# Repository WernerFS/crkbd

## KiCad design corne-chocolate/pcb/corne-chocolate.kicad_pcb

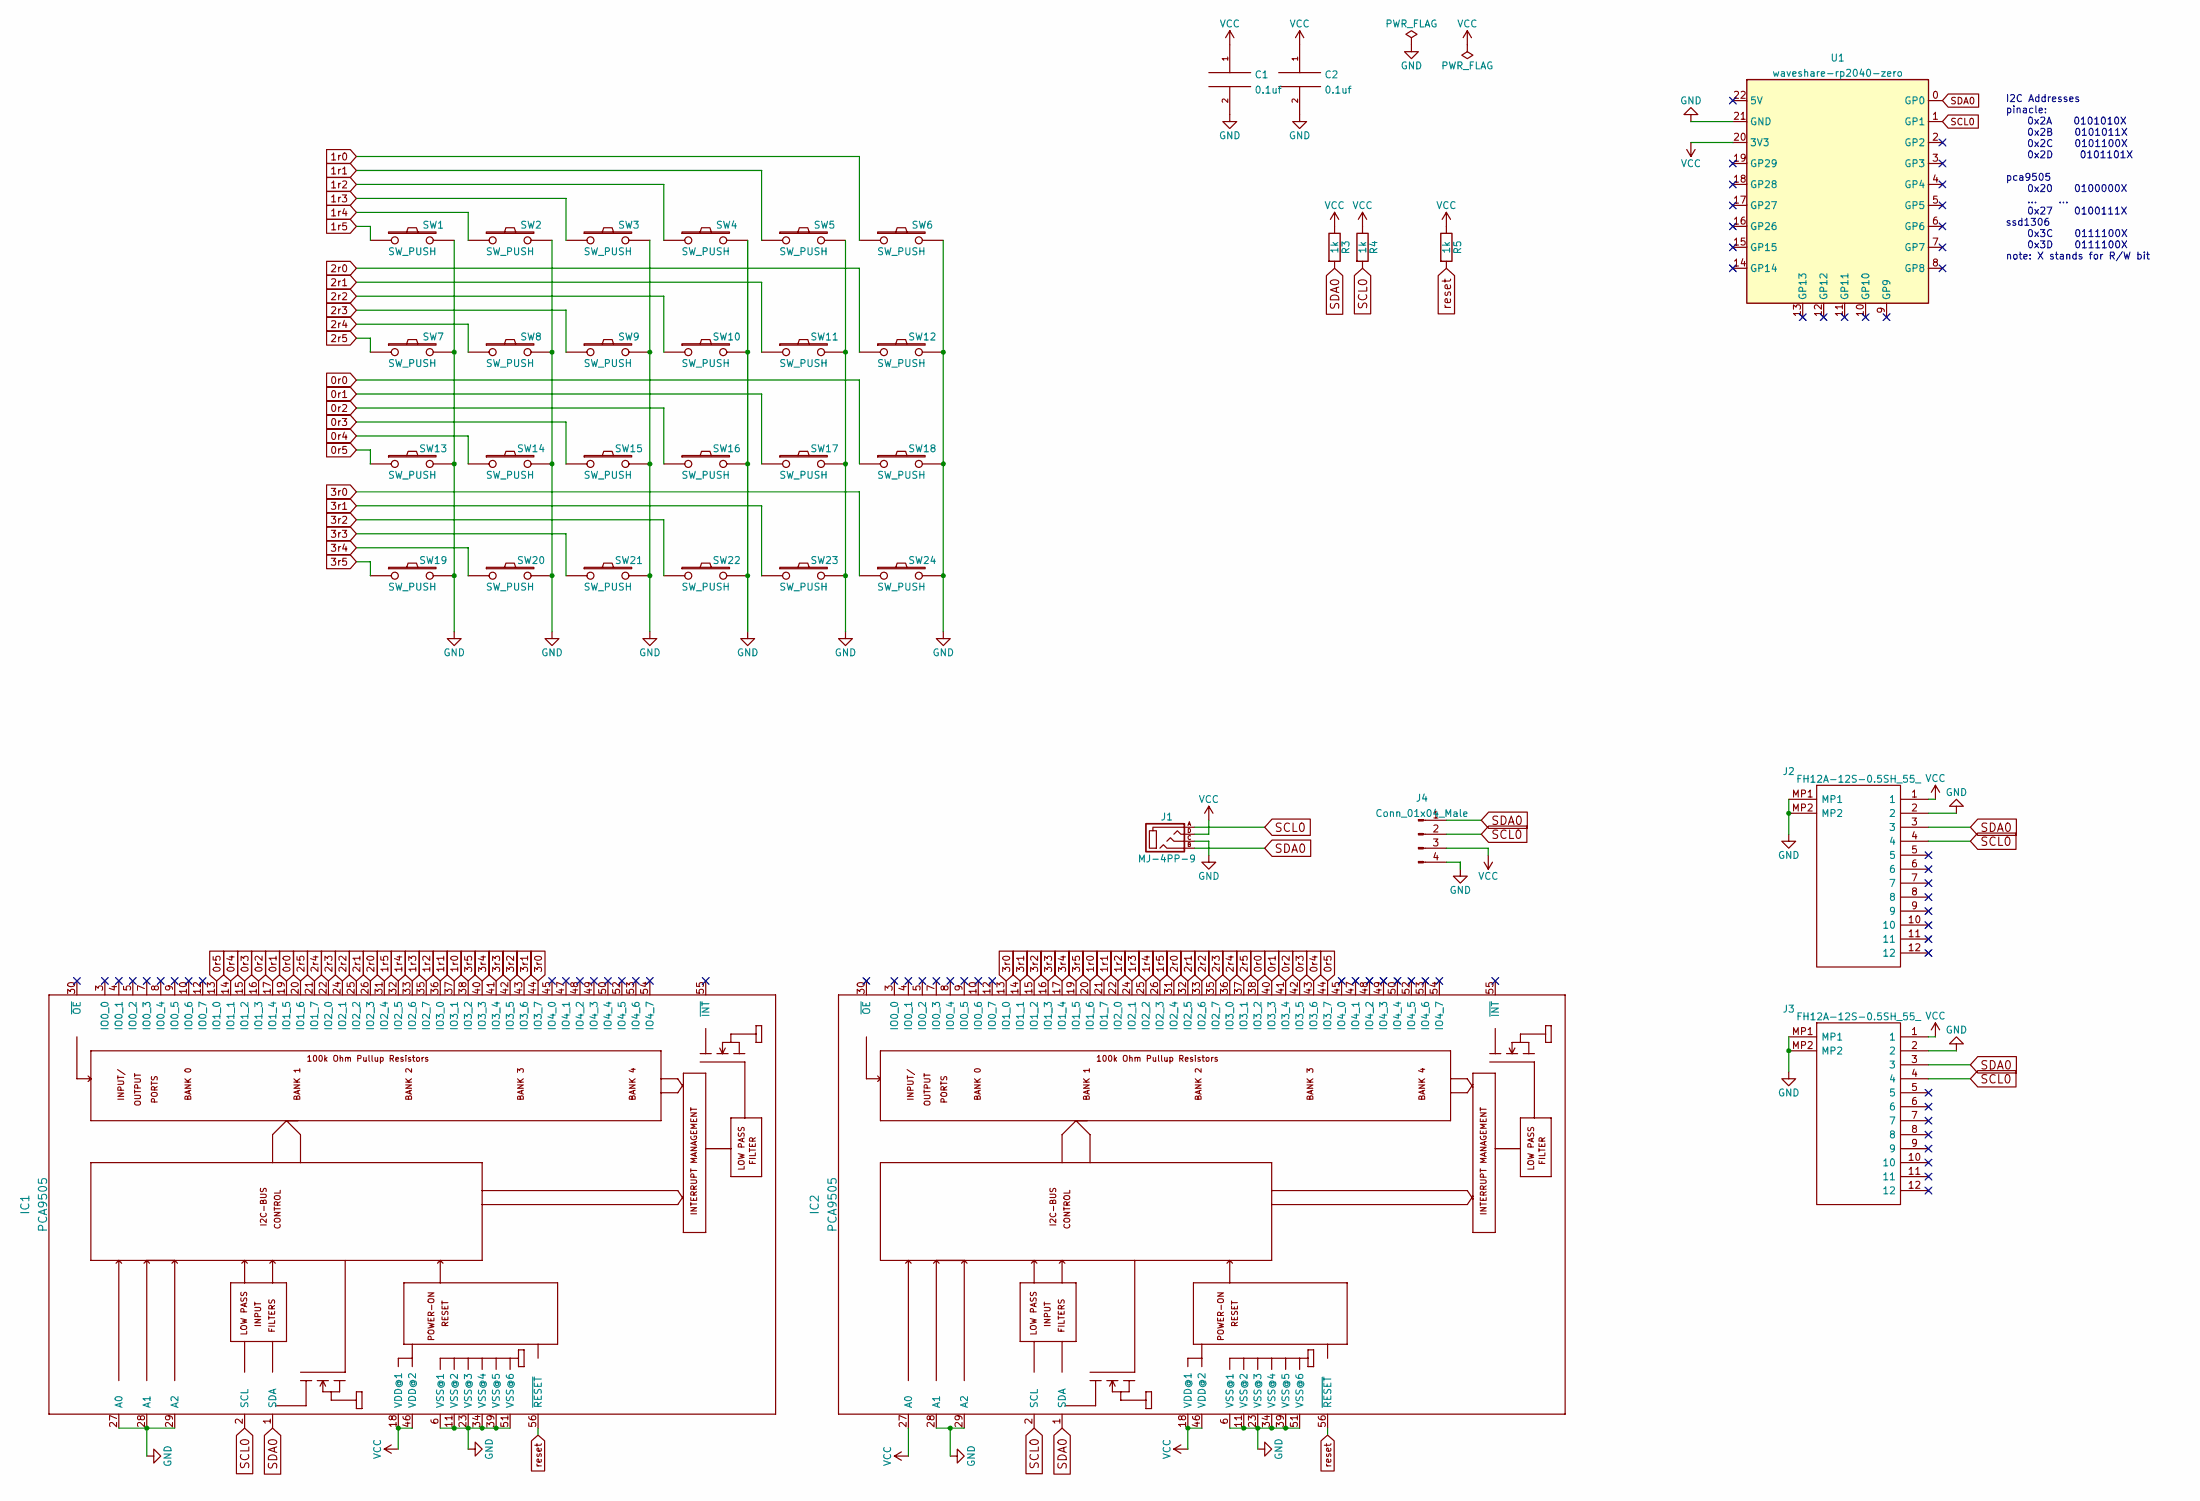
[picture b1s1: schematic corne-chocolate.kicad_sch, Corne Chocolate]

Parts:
C1, C2: 0.1uf; C_0805_2012Metric_Pad1.18x1.45mm_HandSolder
IC1, IC2: PCA9505; TSSOP-56_7x14mm_P0.5mm_mr
J1: MJ-4PP-9; 4-ring-jack-mr
J2, J3: FH12A-12S-0.5SH_55_; FH12A12S05SH55; Mouser Part Number 798-FH12A-12S0.5SH55
J4: Conn_01x04_Male; PinHeader_1x04_P2.54mm_Vertical
R3, R4, R5: 1k; R_0805_2012Metric_Pad1.20x1.40mm_HandSolder
SW1, SW2, SW3, SW4, SW5, SW6, SW7, SW8, SW9, SW10, SW11, SW12, SW13, SW14, SW15, SW16, SW17, SW18, SW19, SW20, SW21, SW22, SW23, SW24: SW_PUSH; kbd-switches
U1: waveshare-rp2040-zero; rp2040-zero-mr

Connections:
0r0: IC1.19 (IO1_5), IC2.38 (IO3_2), SW18.1
0r1: IC1.17 (IO1_4), IC2.40 (IO3_3), SW17.1
0r2: IC1.16 (IO1_3), IC2.41 (IO3_4), SW16.1
0r3: IC1.15 (IO1_2), IC2.42 (IO3_5), SW15.1
0r4: IC1.14 (IO1_1), IC2.43 (IO3_6), SW14.1
0r5: IC1.13 (IO1_0), IC2.44 (IO3_7), SW13.1
1r0: IC1.37 (IO3_1), IC2.20 (IO1_6), SW6.1
1r1: IC1.36 (IO3_0), IC2.21 (IO1_7), SW5.1
1r2: IC1.35 (IO2_7), IC2.22 (IO2_0), SW4.1
1r3: IC1.33 (IO2_6), IC2.24 (IO2_1), SW3.1
1r4: IC1.32 (IO2_5), IC2.25 (IO2_2), SW2.1
1r5: IC1.31 (IO2_4), IC2.26 (IO2_3), SW1.1
2r0: IC1.26 (IO2_3), IC2.31 (IO2_4), SW12.1
2r1: IC1.25 (IO2_2), IC2.32 (IO2_5), SW11.1
2r2: IC1.24 (IO2_1), IC2.33 (IO2_6), SW10.1
2r3: IC1.22 (IO2_0), IC2.35 (IO2_7), SW9.1
2r4: IC1.21 (IO1_7), IC2.36 (IO3_0), SW8.1
2r5: IC1.20 (IO1_6), IC2.37 (IO3_1), SW7.1
3r0: IC1.44 (IO3_7), IC2.13 (IO1_0), SW24.1
3r1: IC1.43 (IO3_6), IC2.14 (IO1_1), SW23.1
3r2: IC1.42 (IO3_5), IC2.15 (IO1_2), SW22.1
3r3: IC1.41 (IO3_4), IC2.16 (IO1_3), SW21.1
3r4: IC1.40 (IO3_3), IC2.17 (IO1_4), SW20.1
3r5: IC1.38 (IO3_2), IC2.19 (IO1_5), SW19.1
GND: C1.2, C2.2, IC1.6 (VSS@1), IC1.11 (VSS@2), IC1.23 (VSS@3), IC1.27 (A0), IC1.28 (A1), IC1.29 (A2), IC1.34 (VSS@4), IC1.39 (VSS@5), IC1.51 (VSS@6), IC2.6 (VSS@1), IC2.11 (VSS@2), IC2.23 (VSS@3), IC2.28 (A1), IC2.29 (A2), IC2.34 (VSS@4), IC2.39 (VSS@5), IC2.51 (VSS@6), J1.C, J2.2, J2.MP1, J2.MP2, J3.2, J3.MP1, J3.MP2, J4.4, SW1.2, SW2.2, SW3.2, SW4.2, SW5.2, SW6.2, SW7.2, SW8.2, SW9.2, SW10.2, SW11.2, SW12.2, SW13.2, SW14.2, SW15.2, SW16.2, SW17.2, SW18.2, SW19.2, SW20.2, SW21.2, SW22.2, SW23.2, SW24.2, U1.21 (GND)
SCL0: IC1.2 (SCL), IC2.2 (SCL), J1.A, J2.4, J3.4, J4.2, R4.2, U1.1 (GP1)
SDA0: IC1.1 (SDA), IC2.1 (SDA), J1.B, J2.3, J3.3, J4.1, R3.2, U1.0 (GP0)
VCC: C1.1, C2.1, IC1.18 (VDD@1), IC1.46 (VDD@2), IC2.18 (VDD@1), IC2.27 (A0), IC2.46 (VDD@2), J1.D, J2.1, J3.1, J4.3, R3.1, R4.1, R5.1, U1.20 (3V3)
reset: IC1.56 (~RESET), IC2.56 (~RESET), R5.2

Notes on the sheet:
I2C Addresses pinacle: 0x2A 0101010X 0x2B 0101011X 0x2C 0101100X 0x2D 0101101X pca9505 0x20 0100000X ... ... 0x27 0100111X ssd1306 0x3C 0111100X 0x3D 0111100X note: X stands for R/W bit

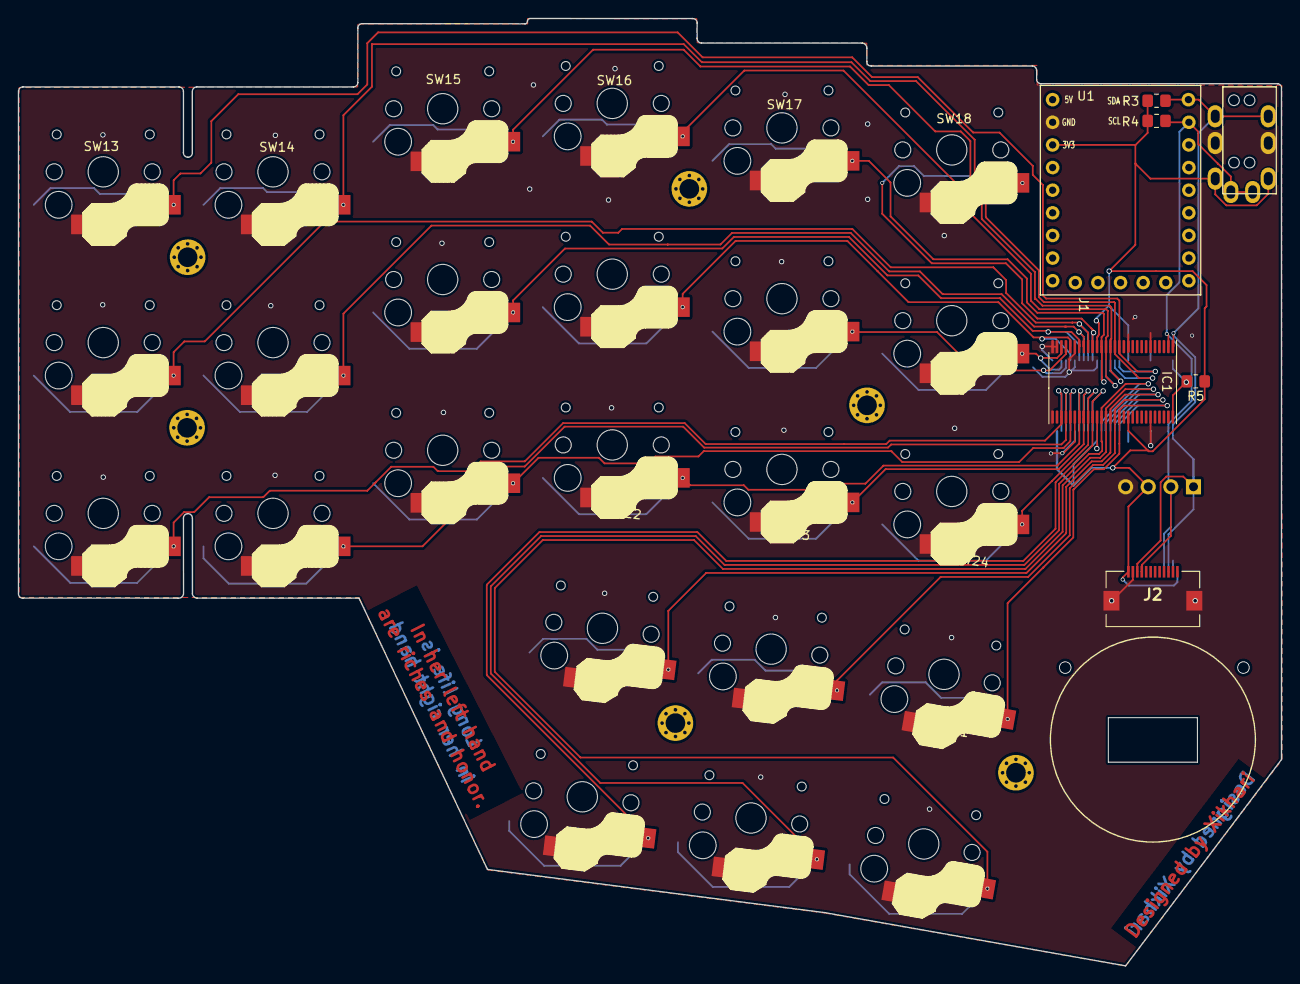
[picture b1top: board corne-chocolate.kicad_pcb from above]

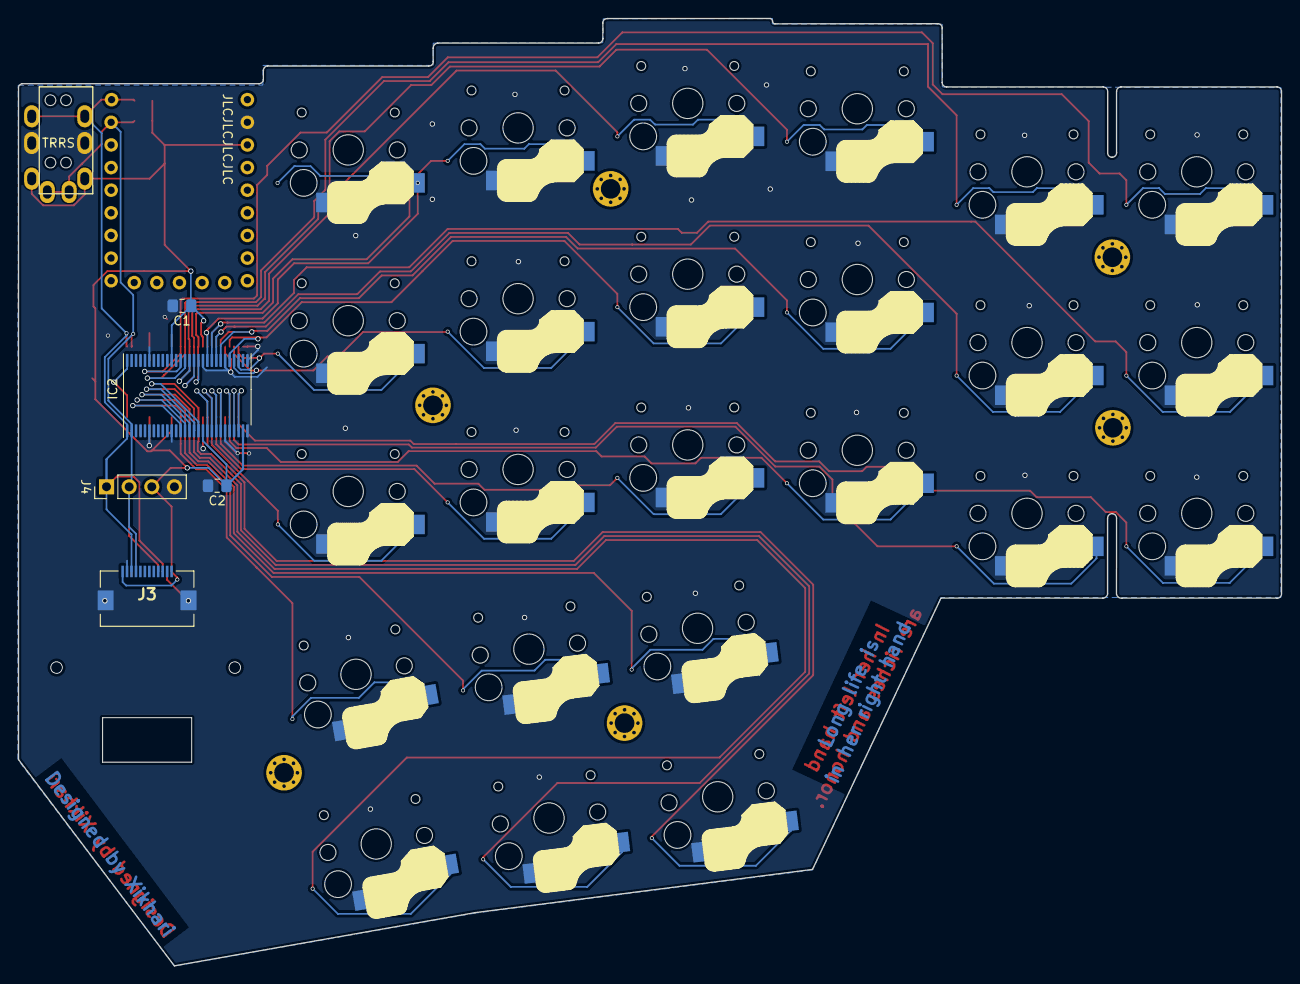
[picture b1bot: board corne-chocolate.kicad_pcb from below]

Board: 2 copper layers, 141.7 x 106.3 mm, 36 parts (5 on the bottom side), 29 nets.

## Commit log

2022-02-14 rp2040 v0
